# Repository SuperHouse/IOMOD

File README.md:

# IOMOD Multi-Purpose I/O Module

*Copyright 2025 SuperHouse Automation Pty Ltd  
[www.superhouse.tv]()*

IOMOD is a mechanical and electrical convention for creating pluggable 
I/O modules for use in test systems and other projects.

The module pinout allows for either I2C or SPI connections to modules, 
and up to 8 I/O pins per module. Modules can also optionally support two 
power domains so that data connections to the host can be at a different 
voltage to connections to the target device.

4 reference implementations have been created so far:

 * AD5593R (I2C)
 * MCP23008 (I2C)
 * MCP23S08 (SPI)
 * Serial Wombat 8B (I2C)

These reference implementations have been designed "upside down", so 
that when they are assembled the parts will be underneath the module. 
This allows the top of the module to be totally flat except for the tops 
of the header pins and their solder joints.

Note: The format is DIP, but it's NOT on a 0.1" grid! That means you
can't plug it into a breadboard. The format is 2mm pitch metric DIP with
10mm row spacing center-to-center. An adapter module design is also 
provided to allow easy use in a breadboard.

Originally developed for the [Testomatic PCB test jig system](https://github.com/superhouse/testomatic).
The Testomatic chassis includes sockets for 7 IOMODs, allowing different 
modules to be installed based on the specific requirements of the test 
plan for the Device Under Test.

## IOMOD Pinout

IOMOD designs are not required to implement all signals. Typically an I2C-based 
module will leave the SPI-related pins unconnected, and vice versa. Modules 
may also omit signals such as the active-low interrupt output or 
the reset pin, and they don't need to implement all 8 GPIO signals.

For example, a module designed specifically for a high-speed SPI 
single-channel high-precision ADC may implement a single GPIO and leave 
the rest unconnected. This is perfectly valid if it suits your use-case.

Modules may also choose to fully isolate the power domains, with a 
floating GND on the I/O side split from the signal GND on the control side. 
The reference designs included here tie both GND pins together as a 
common reference, but if you want to design a module with full galvanic 
isolation you can choose to keep the GND pins separated from each other.

| Pin   | Name  | Use                                       |
|-------|-------|-------------------------------------------|
| 1     | VBUS  | Voltage for control interface             |
| 2     | !RST  | Reset input to module (active low)        |
| 3     | !INT  | Interrupt output from module (active low) |
| 4     | SDA   | I2C data                                  |
| 5     | SCL   | I2C clock                                 |
| 6     | !CS   | SPI chip select (active low)              |
| 7     | MOSI  | SPI MOSI                                  |
| 8     | MISO  | SPI MISO                                  |
| 9     | SCK   | SPI clock                                 |
| 10    | LGND  | Logic ground                              |
| 11    | IOGND | I/O ground                                |
| 12-19 | IOx   | I/O pins                                  |
| 20    | VIO   | Voltage for I/O pins                      |

## IOMOD Mechanical Dimensions

## 2mm-to-0.1" Adapter

## Labelling

A 3D-printed cap design is included that can be glued onto the top of 
the module to give it a large flat area for labels. A dab of Loctite 
Extreme Gel or other suitable glue will hold it in place. It has recesses 
to allow it to sit down over the ends of the header pins.

Labels for the reference designs are included as an Affinity document 
and an A4 PDF. The labels have tabs that wrap underneath the module 
to hold the label firmly in place.

## Insertion / Removal Tool

A 3D-printed tool design is included to make it easier to insert and 
remove modules from a carrier board. Testomatic has 7 IOMODs mounted 
close together so they're tricky to get out with your fingers.

The tool uses a compliant-mechanism hinge. The hinge is a little fragile 
but seems to work OK when printed in PLA. It may be more durable in PETG.

## IOMOD-AD5593R

This variant is designed to be a generic I/O module that provides basic
features to cover typical use cases where high ADC precision, etc is
not required. It's very flexible because it can handle both analog and 
digital input and output with true analog output via the DAC, but unfortunately 
the AD5593R chips are quite expensive.

**Features**

 * AD5593R I/O expander.
 * I2C interface.
 * 8 I/O pins.
 * 3.3V or 5V control interface.
 * 3.3V or 5V I/O interface.
 * Every pin can be individually configured.
 * Digital I/O on every pin.
 * 12-bit ADC on every pin.
 * 12-bit DAC on every pin.

For use with Arduino, see Rob Tillaart's excellent library at [github.com/RobTillaart/AD5593R](https://github.com/RobTillaart/AD5593R)

## IOMOD-MCP23008

This variant is based on the extremely popular MCP23008 I2C I/O expander 
chip, which means it has excellent driver support. However, it is only 
capable of digital input and output. It doesn't support analog I/O at all. 
This makes it less flexible than the AD5593R module, but probably simpler 
to set up in terms of software support. It's also significantly cheaper. 

**Features**

 * MCP23008 I/O expander.
 * I2C interface.
 * 8 I/O pins.
 * 3.3V or 5V control interface.
 * 3.3V or 5V I/O interface.
 * Digital I/O on every pin.

## IOMOD-MCP23S08

This variant has the same features as the MCP23008 module, except that it 
uses SPI for communication with the host. It was implemented mostly to 
validate that the IOMOD header format is also useful for SPI-based modules.

**Features**

 * MCP23S08 I/O expander.
 * SPI interface.
 * 8 I/O pins.
 * 3.3V or 5V control interface.
 * 3.3V or 5V I/O interface.
 * Digital I/O on every pin.

## IOMOD-SW8B

This variant is based on 
[SerialWombat from Broadwell Consulting](https://www.serialwombat.com/), 
which is a project to create an extremely flexible I/O expander using 
readily available MCUs. This IOMOD is based on the CH32V003 MCU, the same 
as used on the [SerialWombat 8B](https://www.kickstarter.com/projects/bwci/serial-wombat-8b-i2c-i-o-boards-big-features-small-money).

Because SerialWombat firmware allows advanced functionality to be 
offloaded to the I/O expander, it can be configured by the host and then 
left to handle its own tasks such as driving PWM, reading encoder 
signals, etc.

More information to come.

INSTALLATION
------------
Schematics and PCBs were created in Fusion360 and exported as EAGLE format,
which can be imported back into Fusion360 or various other packages including KiCAD.

CREDITS
-------
Designed by Jonathan Oxer jon@oxer.com.au

DISTRIBUTION
------------
The specific terms of distribution of this project are governed by the
license referenced below.

LICENSE
-------
Licensed under the TAPR Open Hardware License (www.tapr.org/OHL).
The "license" folder within this repository also contains a copy of
this license in plain text format.

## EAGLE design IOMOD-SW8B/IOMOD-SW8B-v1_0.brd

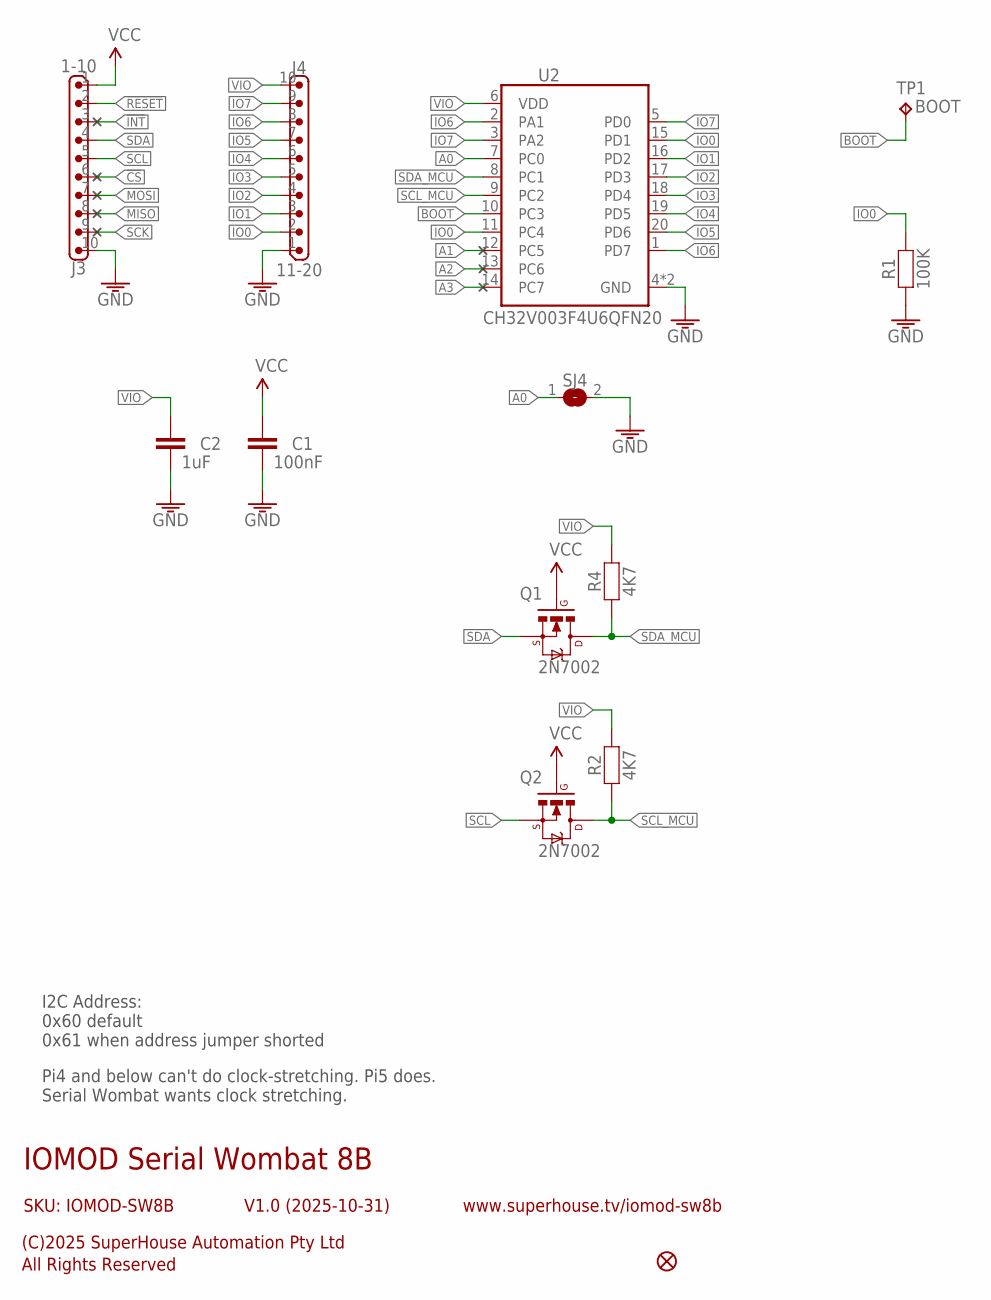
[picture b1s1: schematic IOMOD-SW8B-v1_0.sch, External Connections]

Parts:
C1: 100nF; C0603
C2: 1uF; C0603
FID1: FIDUCIAL1X2.5; FIDUCIAL-1X2.5
J3: 1-10; 1X10-2.00-P-ABOVE
J4: 11-20; 1X10-2.00-P-ABOVE
Q1, Q2: 2N7002; SOT23-3
R1: 100K; R0603
R2, R4: 4K7; R0603
SJ4: SJ-NORMAL; SJ
TP1: BOOT; B1,27
U2: CH32V003F4U6QFN20; QFN-20

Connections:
!CS: J3.6
!INT: J3.3
!RESET: J3.2
A0: SJ4.1, U2.7 (PC0)
A1: U2.12 (PC5)
A2: U2.13 (PC6)
A3: U2.14 (PC7)
BOOT: TP1.TP, U2.10 (PC3)
GND: C1.2, C2.2, J3.10, J4.1, R1.1, SJ4.2, U2.4 (GND), U2.21 (GND)
IO0: J4.2, R1.2, U2.11 (PC4), U2.15 (PD1)
IO1: J4.3, U2.16 (PD2)
IO2: J4.4, U2.17 (PD3)
IO3: J4.5, U2.18 (PD4)
IO4: J4.6, U2.19 (PD5)
IO5: J4.7, U2.20 (PD6)
IO6: J4.8, U2.1 (PD7), U2.2 (PA1)
IO7: J4.9, U2.3 (PA2), U2.5 (PD0)
MISO: J3.8
MOSI: J3.7
SCK: J3.9
SCL: J3.5, Q2.2 (S)
SCL_MCU: Q2.3 (D), R2.1, U2.9 (PC2)
SDA: J3.4, Q1.2 (S)
SDA_MCU: Q1.3 (D), R4.1, U2.8 (PC1)
VCC: C1.1, J3.1, Q1.1 (G), Q2.1 (G)
VIO: C2.1, J4.10, R2.2, R4.2, U2.6 (VDD)

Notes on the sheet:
IOMOD Serial Wombat 8B
V1.0 (2025-10-31)
SKU: IOMOD-SW8B
(C)2025 SuperHouse Automation Pty Ltd
All Rights Reserved
www.superhouse.tv/iomod-sw8b
I2C Address: 0x60 default 0x61 when address jumper shorted
Pi4 and below can't do clock-stretching. Pi5 does. Serial Wombat wants clock stretching.

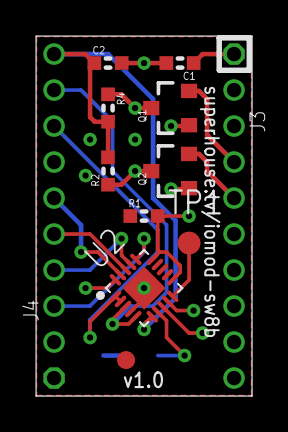
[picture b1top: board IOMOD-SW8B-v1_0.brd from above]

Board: 4 copper layers, 12.0 x 20.0 mm, 13 parts (1 on the bottom side), 17 nets.

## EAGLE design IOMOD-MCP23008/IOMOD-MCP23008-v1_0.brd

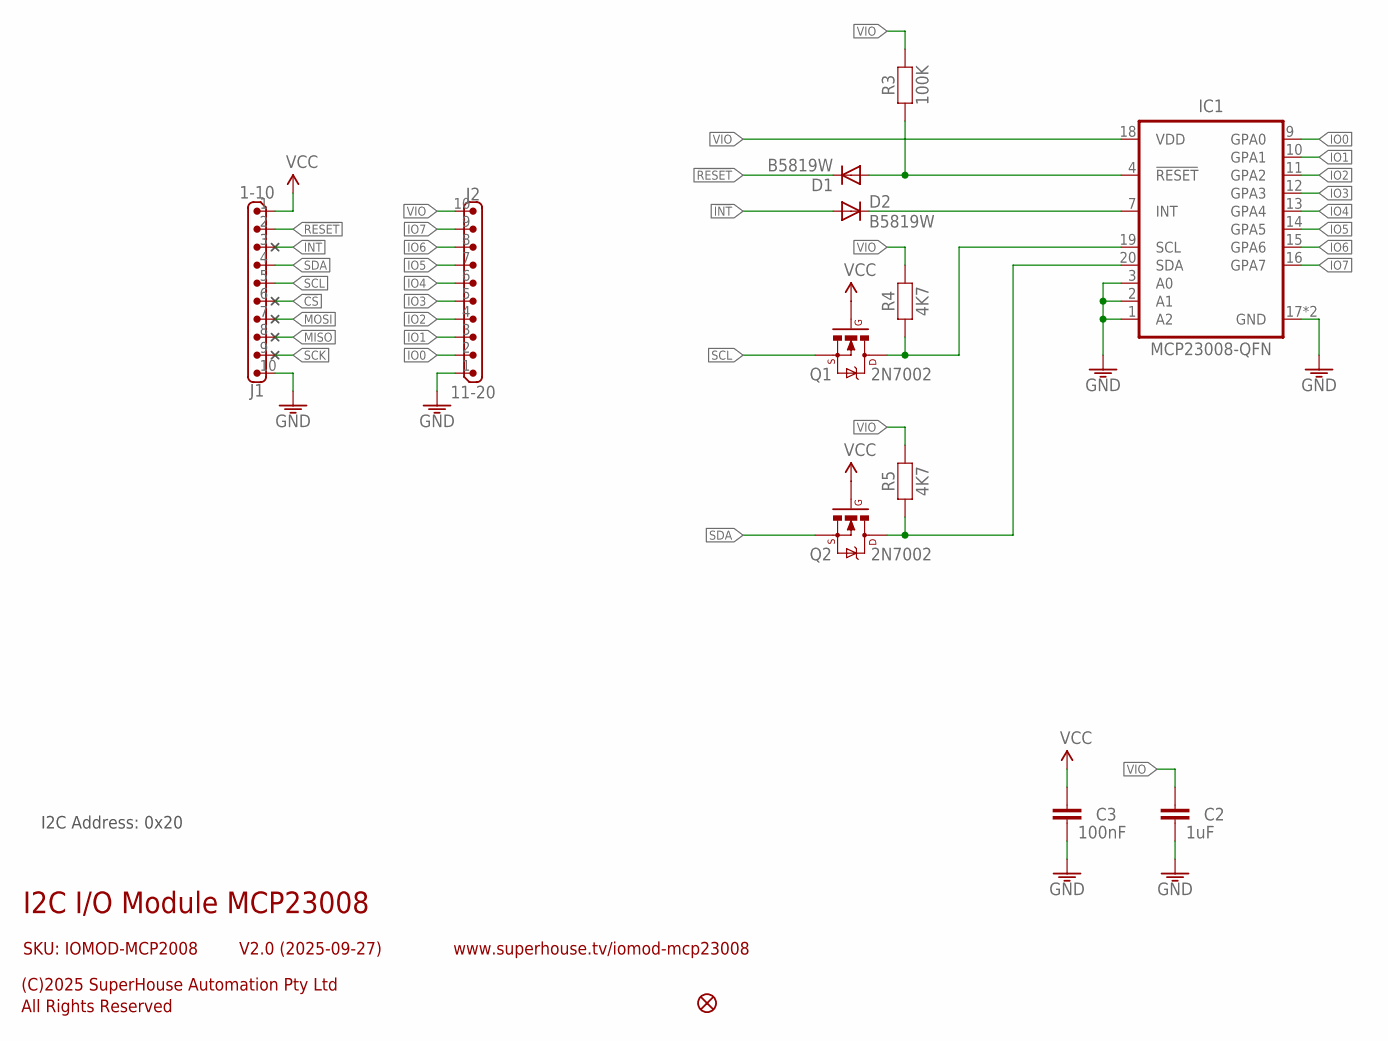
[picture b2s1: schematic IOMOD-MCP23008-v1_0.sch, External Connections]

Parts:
C2: 1uF; C0603
C3: 100nF; C0603
D1, D2: B5819W; SOD-123
FID1: FIDUCIAL1X2; FIDUCIAL-1X2
IC1: MCP23008-QFN; QFN-20
J1: 1-10; 1X10-2.00-P-ABOVE
J2: 11-20; 1X10-2.00-P-ABOVE
Q1, Q2: 2N7002; SOT23-3
R3: 100K; R0603
R4, R5: 4K7; R0603

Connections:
!CS: J1.6
!INT: D2.2 (A), J1.3
!RESET: D1.1 (C), J1.2
GND: C2.2, C3.2, IC1.1 (A2), IC1.2 (A1), IC1.3 (A0), IC1.17 (GND), IC1.TGND (GND), J1.10, J2.1
IO0: IC1.9 (GPA0), J2.2
IO1: IC1.10 (GPA1), J2.3
IO2: IC1.11 (GPA2), J2.4
IO3: IC1.12 (GPA3), J2.5
IO4: IC1.13 (GPA4), J2.6
IO5: IC1.14 (GPA5), J2.7
IO6: IC1.15 (GPA6), J2.8
IO7: IC1.16 (GPA7), J2.9
MISO: J1.8
MOSI: J1.7
unnamed: IC1.20 (SDA), Q2.3 (D), R5.1
unnamed: IC1.19 (SCL), Q1.3 (D), R4.1
unnamed: D2.1 (C), IC1.7 (INT)
unnamed: D1.2 (A), IC1.4 (!RESET), R3.1
SCK: J1.9
SCL: J1.5, Q1.2 (S)
SDA: J1.4, Q2.2 (S)
VCC: C3.1, J1.1, Q1.1 (G), Q2.1 (G)
VIO: C2.1, IC1.18 (VDD), J2.10, R3.2, R4.2, R5.2

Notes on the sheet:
I2C I/O Module MCP23008
V2.0 (2025-09-27)
SKU: IOMOD-MCP2008
(C)2025 SuperHouse Automation Pty Ltd
All Rights Reserved
www.superhouse.tv/iomod-mcp23008
I2C Address: 0x20

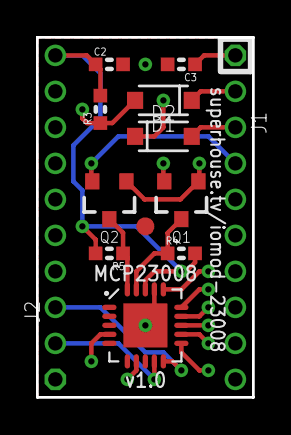
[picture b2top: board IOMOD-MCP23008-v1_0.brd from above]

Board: 4 copper layers, 12.0 x 20.0 mm, 13 parts (0 on the bottom side), 19 nets.

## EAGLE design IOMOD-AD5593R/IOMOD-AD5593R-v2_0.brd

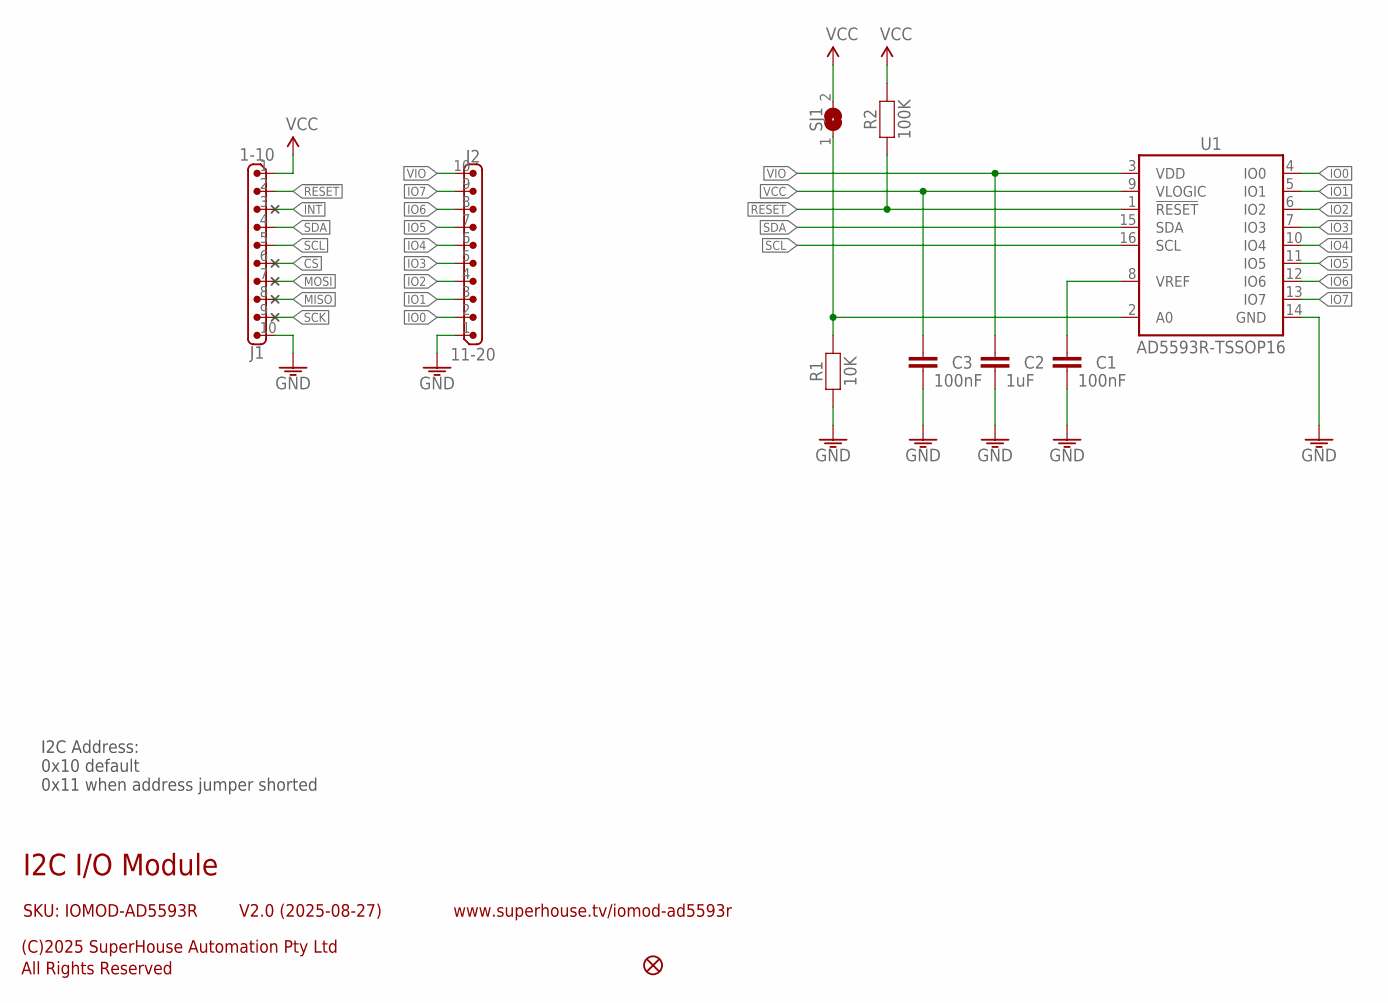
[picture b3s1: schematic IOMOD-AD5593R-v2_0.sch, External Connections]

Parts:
C1, C3: 100nF; C0603
C2: 1uF; C0603
FID1: FIDUCIAL1X2.5; FIDUCIAL-1X2.5
J1: 1-10; 1X10-2.00-P-ABOVE
J2: 11-20; 1X10-2.00-P-ABOVE
R1: 10K; R0603
R2: 100K; R0603
SJ1: SJ-NORMAL; SJ
U1: AD5593R-TSSOP16; TSSOP16

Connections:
!CS: J1.6
!INT: J1.3
!RESET: J1.2, R2.1, U1.1 (!RESET)
GND: C1.2, C2.2, C3.2, J1.10, J2.1, R1.1, U1.14 (GND)
IO0: J2.2, U1.4 (IO0)
IO1: J2.3, U1.5 (IO1)
IO2: J2.4, U1.6 (IO2)
IO3: J2.5, U1.7 (IO3)
IO4: J2.6, U1.10 (IO4)
IO5: J2.7, U1.11 (IO5)
IO6: J2.8, U1.12 (IO6)
IO7: J2.9, U1.13 (IO7)
MISO: J1.8
MOSI: J1.7
unnamed: R1.2, SJ1.1, U1.2 (A0)
unnamed: C1.1, U1.8 (VREF)
SCK: J1.9
SCL: J1.5, U1.16 (SCL)
SDA: J1.4, U1.15 (SDA)
VCC: C3.1, J1.1, R2.2, SJ1.2, U1.9 (VLOGIC)
VIO: C2.1, J2.10, U1.3 (VDD)

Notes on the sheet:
I2C I/O Module
V2.0 (2025-08-27)
SKU: IOMOD-AD5593R
(C)2025 SuperHouse Automation Pty Ltd
All Rights Reserved
www.superhouse.tv/iomod-ad5593r
I2C Address: 0x10 default 0x11 when address jumper shorted

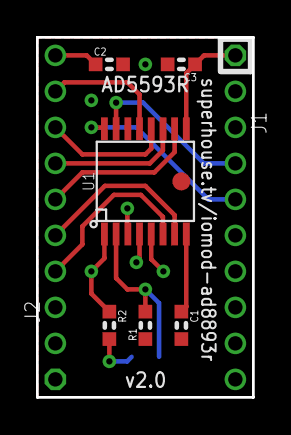
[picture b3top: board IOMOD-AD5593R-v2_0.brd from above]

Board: 4 copper layers, 12.0 x 20.0 mm, 10 parts (1 on the bottom side), 16 nets.

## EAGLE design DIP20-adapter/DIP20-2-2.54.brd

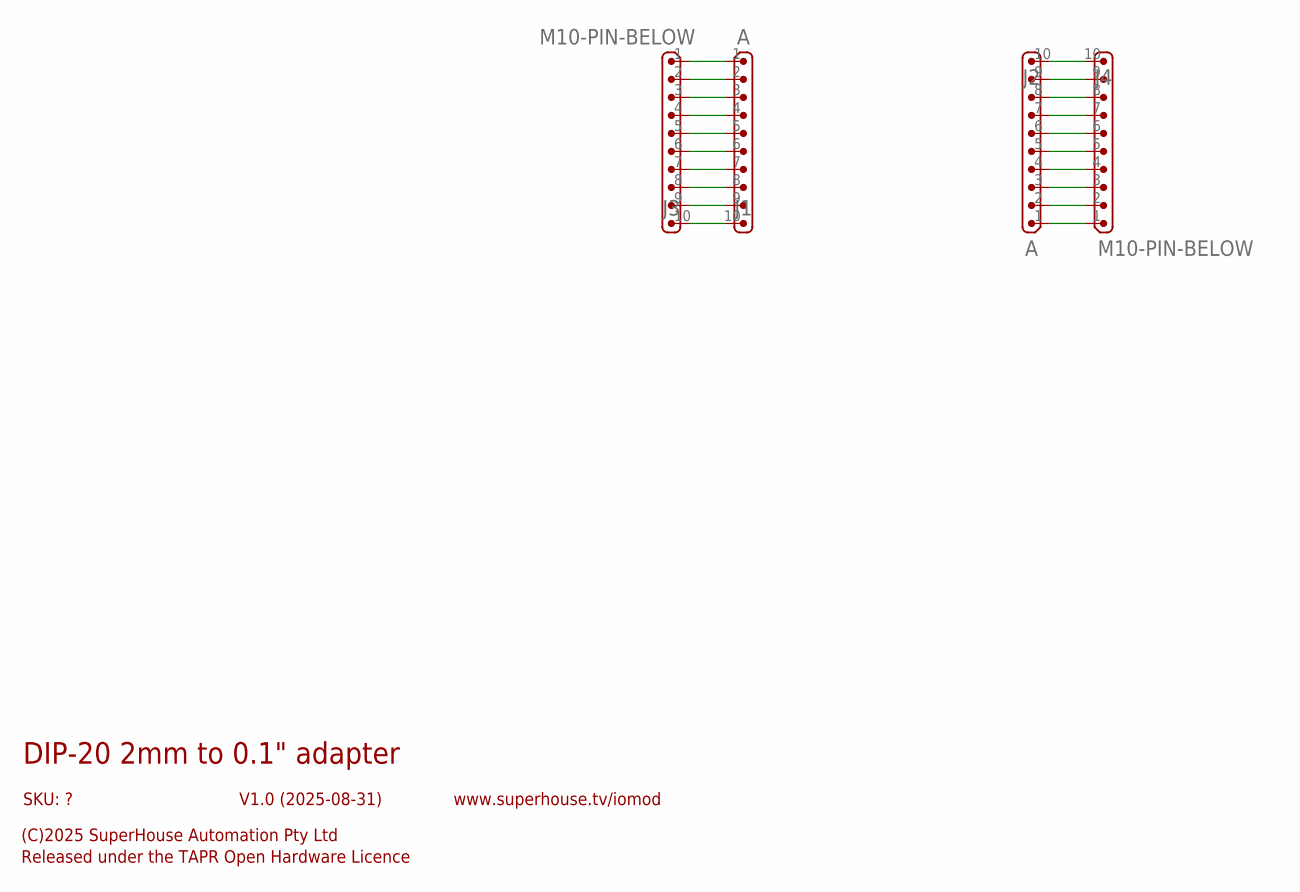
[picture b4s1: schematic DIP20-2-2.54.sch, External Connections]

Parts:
J1, J2: A; 1X10-2.00-S
J3, J4: M10-PIN-BELOW; 1X10-P-BELOW

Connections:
unnamed: J1.1, J3.1
unnamed: J1.2, J3.2
unnamed: J1.3, J3.3
unnamed: J1.4, J3.4
unnamed: J1.5, J3.5
unnamed: J1.6, J3.6
unnamed: J1.7, J3.7
unnamed: J1.8, J3.8
unnamed: J2.1, J4.1
unnamed: J2.2, J4.2
unnamed: J2.3, J4.3
unnamed: J2.4, J4.4
unnamed: J2.5, J4.5
unnamed: J2.6, J4.6
unnamed: J2.7, J4.7
unnamed: J2.8, J4.8
unnamed: J1.9, J3.9
unnamed: J1.10, J3.10
unnamed: J2.9, J4.9
unnamed: J2.10, J4.10

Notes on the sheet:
DIP-20 2mm to 0.1" adapter
V1.0 (2025-08-31)
SKU: ?
(C)2025 SuperHouse Automation Pty Ltd
Released under the TAPR Open Hardware Licence
www.superhouse.tv/iomod

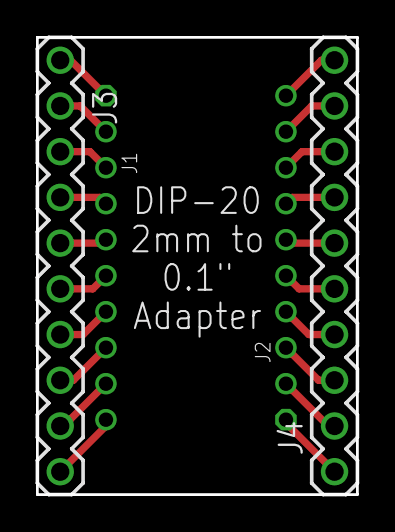
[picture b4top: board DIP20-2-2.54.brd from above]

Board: 2 copper layers, 17.8 x 25.4 mm, 4 parts (0 on the bottom side), 20 nets.

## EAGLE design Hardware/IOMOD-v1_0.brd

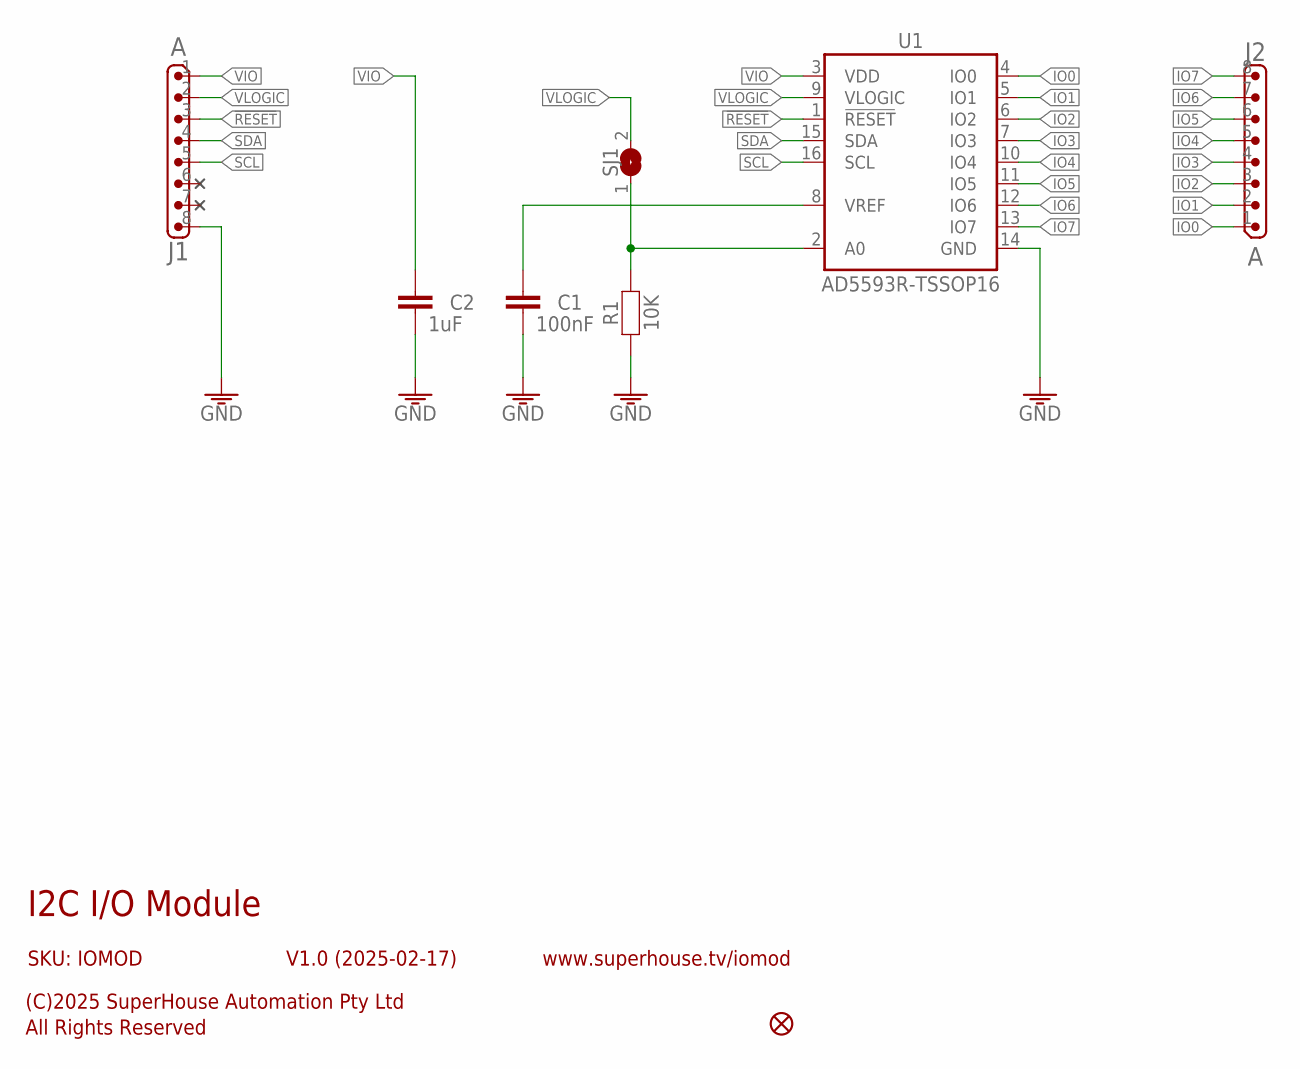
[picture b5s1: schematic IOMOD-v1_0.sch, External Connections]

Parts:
C1: 100nF; C0603
C2: 1uF; C0603
FID1: FIDUCIAL1X2.5; FIDUCIAL-1X2.5
J1, J2: A; 1X8-2.00-P-BELOW
R1: 10K; R0603
SJ1: SJ-NORMAL; SJ
U1: AD5593R-TSSOP16; TSSOP16

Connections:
!RESET: J1.3, U1.1 (!RESET)
GND: C1.2, C2.2, J1.8, R1.1, U1.14 (GND)
IO0: J2.1, U1.4 (IO0)
IO1: J2.2, U1.5 (IO1)
IO2: J2.3, U1.6 (IO2)
IO3: J2.4, U1.7 (IO3)
IO4: J2.5, U1.10 (IO4)
IO5: J2.6, U1.11 (IO5)
IO6: J2.7, U1.12 (IO6)
IO7: J2.8, U1.13 (IO7)
unnamed: R1.2, SJ1.1, U1.2 (A0)
unnamed: C1.1, U1.8 (VREF)
SCL: J1.5, U1.16 (SCL)
SDA: J1.4, U1.15 (SDA)
VIO: C2.1, J1.1, U1.3 (VDD)
VLOGIC: J1.2, SJ1.2, U1.9 (VLOGIC)

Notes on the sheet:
I2C I/O Module
V1.0 (2025-02-17)
SKU: IOMOD
(C)2025 SuperHouse Automation Pty Ltd
All Rights Reserved
www.superhouse.tv/iomod

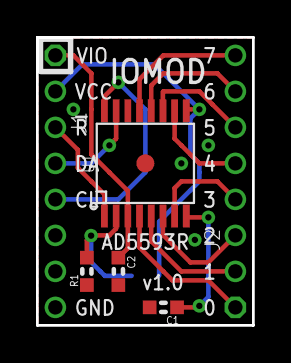
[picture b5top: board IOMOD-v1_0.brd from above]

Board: 2 copper layers, 12.0 x 16.0 mm, 8 parts (1 on the bottom side), 16 nets.

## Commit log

2025-02-22 Initial import of project
2025-02-22 Added Fusion360 archive version of design files.
2025-02-27 Added clarifying note regarding DIP format.
2025-03-10 Added PDF of schematic.
2025-03-10 Added design for 2mm-to-0.1 DIP adapter
2025-06-25 Added link to Testomatic repo
2025-09-24 v2.0 release with major pinout change.
2025-09-24 Added oblique image.
2025-10-27 Added link to Rob's Arduino library
2025-11-27 Started rearranging files
2025-11-27 File rearrangement
2025-11-27 Expanded README in preparation for adding other IOMOD variants.
2025-11-27 Fixed accidental deletion
2025-11-27 Added files for MCP23008 and SW8B versions
2025-11-27 Added 3D-printed caps
2025-11-28 Additional screenshots and expanded README
2025-11-28 Added pic of assembled modules with caps and labels
2025-11-28 Added documentation of pinout.
2025-11-28 Added printable labels
2025-11-28 Added TAPR license file
2025-11-28 Added design files for module puller tool
